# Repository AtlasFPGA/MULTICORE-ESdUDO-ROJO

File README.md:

# MULTICORE-ESdUDO-ROJO
Diseñar la placa - ¡Créalo tu mismo! de coste más reducido para la Fpga CYC1000 con una bluepill STM32F103C8T6

Group ATLAS in Telegram: https://t.me/INICIATIVAATLAS

   Se muestra el multicore en desarrollo para cyc1000 de arrow/trenz el cual aloja una fpga Cyclone 10 LP de intel con 25kles y 66 bloques de Bram de 9Kbytes, tiene integrada una memoria de celular de bajo consumo y reducida latencia, siendo una sdram a 166Mhz con 8MBytes en un bus de 16bits, La familia Cyclone 10 LP permite implementar modelos que superan los 400Mhz en sus diseños, manteniendo un bajo consumo. 
También hay que disponer de una bluepill con un STM32F103C8Tx, posee 64Kbytes de Flash y 20Kbytes de sram, con una unidad de proceso ARM cortex M3 de 32bit funcionando a 72Mhz. 

---
# Esquema analógico totalmente configurable por el usuario en el vídeo compuesto de 512 colores.

Nota:

Creamos una tabla para proceder con el ajuste analógico de la salida de vídeo compuesto.

| R3  |     RV1   | VALOR RESISTIVO RAMA COMPOSITE 0  | R4  | RV2  |  VALOR RESISTIVO RAMA COMPOSITE 1|
|:-------------:|------:|------:|------:|------:|------:|
|750 Ohm|0 Ohm|750 Ohm| 80 Ohm| 0 Ohm|80 Ohm|
|1500 Ohm|1000 Ohm|2500 Ohm|80 Ohm|150 Ohm|230 Ohm|

Para Composite 0 la corriente máxima se obtiene con 750 Ohm -> +3,3V/(750_Ohm)= 0,0044 Amperios

Para Composite 0 la corriente mínima se obtiene con 2500 Ohm -> +3,3V/(2500_Ohm)= 0,00132 Amperios

Para Composite 1 la corriente máxima se obtiene con 80 Ohm -> +3,3V/(80_Ohm)= 0,04125 Amperios -> La CYCLONE 10 LP esta limitada a 12Miliamperios ¿Lo fundimos?

Para Composite 1 la corriente mínima en el diseño propuesto se obtiene con 230 Ohm -> +3,3V/(230_Ohm)= 0,014347926 Amperios -> Por encima de la limitación de corriente 12Miliamperios

Luego hay que calcular que valores de resistencia usar, en Composite 1 en las dos posiciones extremas se drena más corriente por pin.
También vemos que aporta más corriente Composite1 un valor más fuerte que Composite0, por lo que tenemos bien ordenadas las lineas por donde van las señales, pero al ser hardware programable, imaginamos que nos equivocamos, esta es una de las grandes cualidades de una FPGA, con una simple reordenadión de pineado y reetiquetado todo funciona perfectamente,es por esto que muchos diseños actualmente son programables ya sean microcontroladores, cplds o fpgas.

Luego la pregunta es, que resistencia en serie a +3,3V coloco para no fundir un pin de... ¿la preciada FPGA?
doce miliamperios = 0,012_Amperios = +3,3_Voltios/Resistencia_protección_pin

Resistencia_protección_pin = 275 Ohm

Es lo más importante dado que la FPGA tiene limitada la cantidad de corriente que es capaz de entregar, y hacerle una conexión muy baja en resistencia puede fundir o dicho pin o parte de los pines de salida de la fpga, raramente toda la FPGA.

Sus resistencias se suman, la posición de las resistencias fijas es para proteger los circuitos y limitar la corriente, en realidad hemos puesto el valor represantado con el mayor valor resistivo y el menor de todos.

# Pero como siempre pasa os he mentido, porque... ¿Realmente llega a 0V cuando el televisor recoge la señal?

El caso de los condensadores/capacitores de filtrado es algo más complejo dado que las ramas que estan en serie siguen esta ley (Condensador=Capacitor):
1/Condensador_equivalente = 1/Condensador_serie1 + 1/Condensador_serie2 + 1/Condensador_serie3 + ... + 1/Condensador_serieN
Pero como vamos a usar valores del mismo condensador tenemos una rama preparada en serie.
El condensador usado para el montaje son 6 condensadores de 22 pico faradios, ya ser verán si se colocan todos o no, una capacidad bastante pequeña.
1 Mili = 0'001 Faradios
1 Nano = 0'000001 Faradios
1 Pico = 0'000000001 Faradios

Entondes en realidad usamos condensadores/capacitores de:
22 Pico Faradios = 0'000000022 Faradios

cuando hacemos y despejamos esta ecuación 1/Faradios_rama_serie = 1/0'000000022_F + 1/0'000000022_F
Sale un resultado de Faradios_rama_serie = 1/0'000000011 Faradios y en lenguaje de pico -> 11 pico Faradios

Cuando hay condensadore/capacitores en paralelo se suman sus capacidades:
Podemos no filtrar la señal -> 0Faradios pero esto nunca se cumple y menos con señales generadas a tanta frecuencia las pistas siempre tienen un contenido continuo de capacitancia, por eso siempre aparecen modelizaciones de spice.

Usando los 2 condensadores en una sola rama en serie:
Una capacidad de 11 Pico faracios.

Poniendo un Condensador de 22 picofaracios entre la señal de salida de la fpga y GND.
Una capacidad de 22 Pico faradios.

Poniendo los 2 condensadores en paralelo se suman sus capacidades, (Tampoco es verdad si los condensaores estan limitados en voltaje):
Pero bueno digamos que todo es ideal y son 44 Pico Faradios.

La maxima capacidad es usar 2 condensadores en paralelo más una rama de condensadores en serie:
22 Pico Faradios + 22 Pico Faradios + 11 Pico Faradios = 55 Pico Faradios.

Luego con 4 condensadores en la disposición del circuito podemos tener estas capacidades.

Practicamente 0 Faradios , 0'000000022 Faradios,0'000000033 Faradios ,0'000000044 Faradios y 0'000000055 Faradios
Hay un modo que he puesto su filtrado pero no esta explicado.
Pero se vé lo útil de tener la dispoción de filtrado en capacidad, por supuesto si alguien quiere filtrar más la señal puede cambiando los modelos de condensador.

Las resistencias tienen un valor fijo en R3 y R4 y al menos tendrían que limitar la corriente al máximo que permite la familia Cyclone 10 Lp.
---
# Esquema ESdUDO V0101

---
# Capas de la placa ESdUDO V0101

---

   Este modelo implementa soluciones de muy baja latencia, al usar envoltorios con máquinas de estado finito para el video compuesto y el teclado.
   
###   https://github.com/TheSonders/COLOR_PAL
   
###   https://github.com/TheSonders/USBKeyboard

   El diseño es de reducido tamaño, permitiendo alojarlo en equipos estropeados y no recuperables.

   En precio asociado a la placa son aproximadamente 6€.
---

#   Una lista de los pocos componentes necesarios

| Unidades  |     descripción      |  Precio medio en tienda física en España |
|----------|:-------------:|------:|
| 8 |  • condensadores de filtrado, ramas serie y paralelo. | ?€|
| 4 |  • resistencias. Dos de ellas prescindibles mediante programacion de pull down en las patillas K1 y L1 de la cyc1000. |  ?€ |
| 2 | • potenciometros de señal para ajustar la intensidad. |    ?€ |
  | numerosos | • Asi como bastantes tiras de pines, machos y hembras también pines apilables usados en arduino. |    ?€ |
  | 1 | • Un condensador electrolítico. |    ?€ |
  | 1 | • Un pulsador. |    ?€ |
  | 1 | • Un puerto usb A. |    ?€ |
  | 1 | • Un puerto de vídeo compuesto. |    ?€ |
  | 1 | • Disponer de una muestra de cyc1000 del programa Europero de fpgas de intel/arrow. |    ?€ |
  | 1 | • Disponer de una bluepill. |    ?€ |
  | 1 | • Así como un módulo i2s de texas instruments MCP5102A. |    ?€ |

--- 
   Es con diferencia el sistema multicore más económico.

Las placas necesarias:

# ¡ATENCIÓN A LA BLUPILL COLOCADA! 
# HAY DOS MODELOS DE BLUEPILL, LA BLUEPILL PLUS, Y LA PRIMERA BLUEPILL.

BLUEPILL STM32F103C8T6 (Usada en el DISEÑO V0101):

https://es.aliexpress.com/item/1005003429884084.html

BLUEPILL STM32F103C8T6 Plus (Necesita adaptación una linea de 5V existe en lugar de GND, se producirá un buen corto si se opta por este modelo),
por lo demás es compatible en un rango de funcionamiento del 99% y tiene un punto que para el programador es interesante  duplica la flash disponible 128Kbytes.

https://m.es.aliexpress.com/item/1005004918334754.html

SD+TFT AZ-Delivery de 1,8Pulgadas:

https://es.aliexpress.com/item/1005005060814683.html

CYC1000 versión mejorada del 2023 TEI0003-03-QFCR4A-CYC1000:

https://shop.trenz-electronic.de/en/TEI0003-03-QFCR4A-CYC1000-with-Cyclone-10-FPGA-8-MB-SDRAM-8-MB-Flash-6.15-x-2.5-cm?c=480

O una muestra en el programa europeo de microfpgas:

https://www.arrow.com/en/family/intel-solutions-europe

Grupo de la iniciativa ATLAS en TELEGRAM:

# https://t.me/INICIATIVAATLAS

Licencia CERN OHL V2 STRICT:

https://ohwr.orgcern_ohl_s_v2.txt

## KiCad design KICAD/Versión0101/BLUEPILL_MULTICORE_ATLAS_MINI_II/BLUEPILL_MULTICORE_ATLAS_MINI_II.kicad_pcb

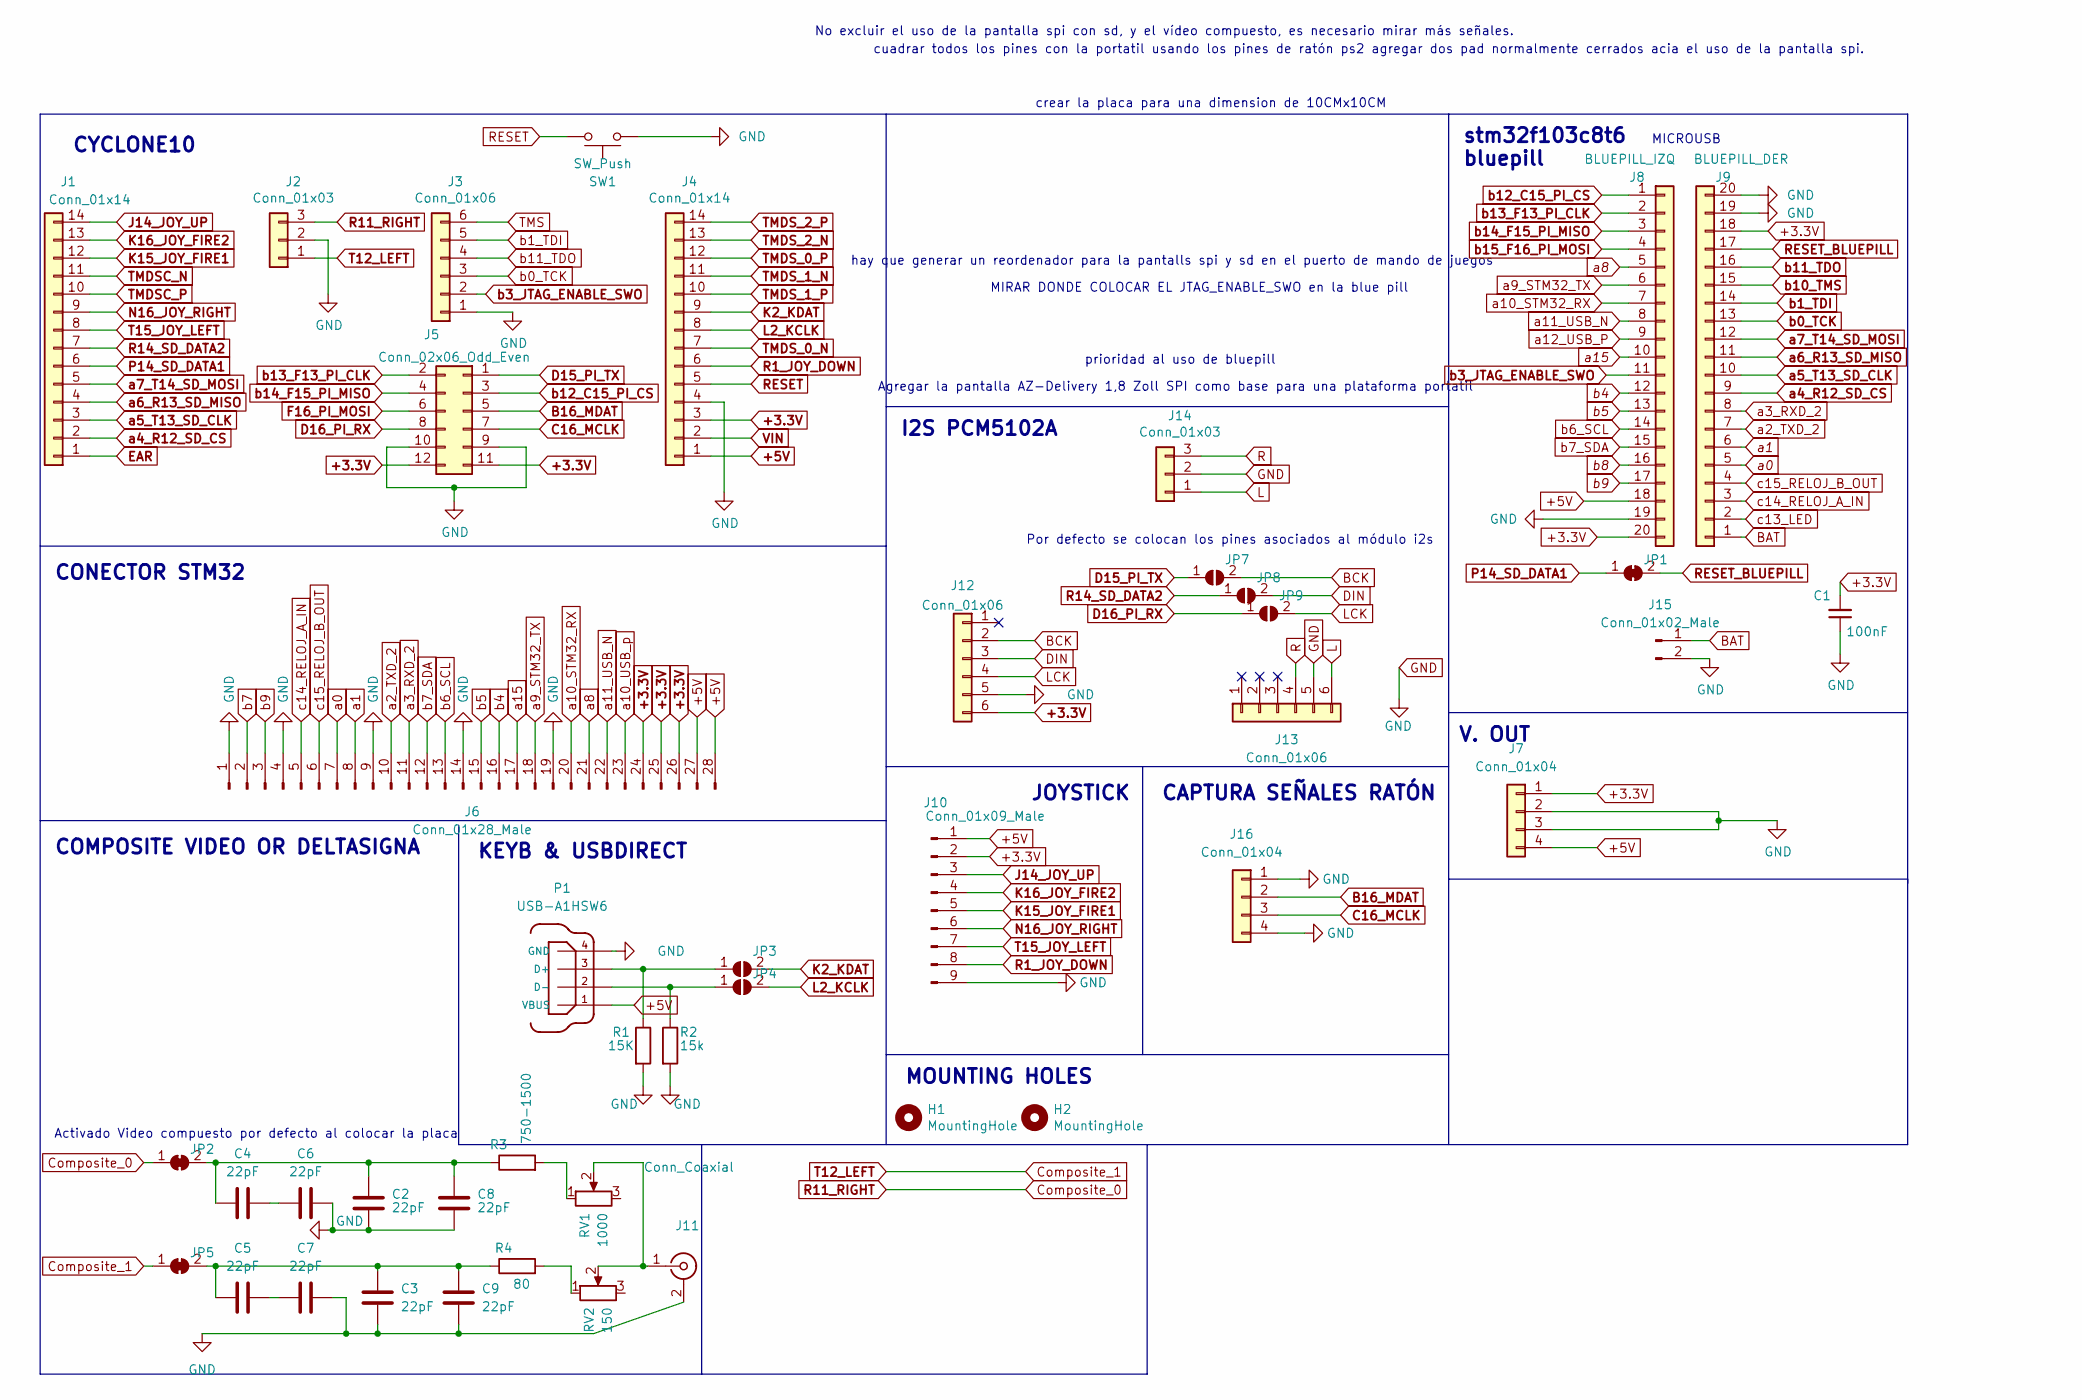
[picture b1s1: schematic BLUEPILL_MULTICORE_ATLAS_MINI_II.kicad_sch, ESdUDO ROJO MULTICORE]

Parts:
C1: 100nF; CP_Radial_D6.3mm_P2.50mm
C2, C3, C4, C5, C6, C7, C8, C9: 22pF; CP_Radial_Tantal_D4.5mm_P2.50mm
H1, H2: MountingHole; MountingHole_3.2mm_M3
J1, J4: Conn_01x14; PinSocket_1x14_P2.54mm_Vertical
J2, J14: Conn_01x03; PinSocket_1x03_P2.54mm_Vertical
J3: Conn_01x06; PinSocket_1x06_P2.54mm_Vertical
J5: Conn_02x06_Odd_Even; PinSocket_2x06_P2.54mm_Vertical
J6: Conn_01x28_Male; PinHeader_1x28_P2.54mm_Horizontal
J7, J16: Conn_01x04; PinHeader_1x04_P2.54mm_Vertical
J8: BLUEPILL_IZQ; PinSocket_1x20_P2.54mm_Vertical
J9: BLUEPILL_DER; PinSocket_1x20_P2.54mm_Vertical
J10: Conn_01x09_Male; PinHeader_1x09_P2.54mm_Vertical
J11: Conn_Coaxial; rca_combined
J12, J13: Conn_01x06; PinHeader_1x06_P2.54mm_Vertical
J15: Conn_01x02_Male; PinSocket_1x02_P2.54mm_Horizontal
JP1, JP2, JP5: SolderJumper_2_Bridged; SolderJumper-2_P1.3mm_Bridged2Bar_RoundedPad1.0x1.5mm
JP3, JP4, JP7, JP8, JP9: SolderJumper_2_Open; SolderJumper-2_P1.3mm_Open_RoundedPad1.0x1.5mm
P1: USB-A1HSW6; OST_USB-A1HSW6
R1: 15K; R_Axial_DIN0309_L9.0mm_D3.2mm_P2.54mm_Vertical
R2: 15k; R_Axial_DIN0309_L9.0mm_D3.2mm_P2.54mm_Vertical
R3: 750-1500; R_Axial_DIN0309_L9.0mm_D3.2mm_P2.54mm_Vertical
R4: 80; R_Axial_DIN0309_L9.0mm_D3.2mm_P2.54mm_Vertical
RV1: 1000; Potentiometer_Bourns_3339H_Vertical
RV2: 150; Potentiometer_Bourns_3339H_Vertical
SW1: SW_Push; SW_PUSH_6mm

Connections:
+3.3V: C1.2, J4.3, J5.11, J5.12, J6.24, J6.25, J6.26, J7.1, J8.20, J9.18, J10.2, J12.6
+5V: J4.1, J6.27, J6.28, J7.4, J8.18, J10.1, P1.1 (VBUS)
B16_MDAT: J5.5, J16.2
BAT: J9.1, J15.1
BCK: J12.2, JP7.2 (B)
C16_MCLK: J5.7, J16.3
Composite_0: J2.3, JP2.1 (A)
Composite_1: J2.1, JP5.1 (A)
D15_PI_TX: J5.1, JP7.1 (A)
D16_PI_RX: J5.8, JP9.1 (A)
DIN: J12.3, JP8.2 (B)
EAR: J1.1
F16_PI_MOSI: J5.6
GND: C1.1, C2.2, C3.2, C6.2, C7.2, C8.2, C9.2, J2.2, J3.1, J4.4, J5.9, J5.10, J6.1, J6.4, J6.9, J6.14, J6.19, J7.2, J7.3, J8.19, J9.19, J9.20, J10.9, J11.2 (Ext), J12.5, J13.5, J14.2, J15.2, J16.1, J16.4, P1.4 (GND), R1.2, R2.2, SW1.2
J14_JOY_UP: J1.14, J10.3
K2_KDAT: J4.9, JP3.2 (B)
K15_JOY_FIRE1: J1.12, J10.5
K16_JOY_FIRE2: J1.13, J10.4
L: J13.6, J14.1
L2_KCLK: J4.8, JP4.2 (B)
LCK: J12.4, JP9.2 (B)
N16_JOY_RIGHT: J1.9, J10.6
unnamed: C2.1, C4.1, C8.1, JP2.2 (B), R3.1
unnamed: C3.1, C5.1, C9.1, JP5.2 (B), R4.1
unnamed: C4.2, C6.1
unnamed: C5.2, C7.1
unnamed: J11.1 (In), RV1.2, RV2.2
unnamed: JP3.1 (A), P1.3 (D+), R1.1
unnamed: JP4.1 (A), P1.2 (D-), R2.1
unnamed: R3.2, RV1.1
unnamed: R4.2, RV2.1
P14_SD_DATA1: J1.6, JP1.1 (A)
R: J13.4, J14.3
R1_JOY_DOWN: J4.6, J10.8
R14_SD_DATA2: J1.7, JP8.1 (A)
RESET: J4.5, SW1.1
RESET_BLUEPILL: J9.17, JP1.2 (B)
T15_JOY_LEFT: J1.8, J10.7
TMDSC_N: J1.11
TMDSC_P: J1.10
TMDS_0_N: J4.7
TMDS_0_P: J4.12
TMDS_1_N: J4.11
TMDS_1_P: J4.10
TMDS_2_N: J4.13
TMDS_2_P: J4.14
TMS: J3.6
VIN: J4.2
a0: J6.7, J9.5
a1: J6.8, J9.6
a2_TXD_2: J6.10, J9.7
a3_RXD_2: J6.11, J9.8
a4_R12_SD_CS: J1.2, J9.9
a5_T13_SD_CLK: J1.3, J9.10
a6_R13_SD_MISO: J1.4, J9.11
a7_T14_SD_MOSI: J1.5, J9.12
a8: J6.21, J8.5
a9_STM32_TX: J6.18, J8.6
a10_STM32_RX: J6.20, J8.7
a10_USB_p: J6.23
a11_USB_N: J6.22, J8.8
a12_USB_P: J8.9
a15: J6.17, J8.10
b0_TCK: J3.3, J9.13
b1_TDI: J3.5, J9.14
b3_JTAG_ENABLE_SWO: J3.2, J8.11
b4: J6.16, J8.12
b5: J6.15, J8.13
b6_SCL: J6.13, J8.14
b7: J6.2
b7_SDA: J6.12, J8.15
b8: J8.16
b9: J6.3, J8.17
b10_TMS: J9.15
b11_TDO: J3.4, J9.16
b12_C15_PI_CS: J5.3, J8.1
b13_F13_PI_CLK: J5.2, J8.2
b14_F15_PI_MISO: J5.4, J8.3
b15_F16_PI_MOSI: J8.4
c13_LED: J9.2
c14_RELOJ_A_IN: J6.5, J9.3
c15_RELOJ_B_OUT: J6.6, J9.4

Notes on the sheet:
No excluir el uso de la pantalla spi con sd, y el vídeo compuesto, es necesario mirar más señales.
Por defecto se colocan los pines asociados al módulo i2s
hay que generar un reordenador para la pantalls spi y sd en el puerto de mando de juegos
prioridad al uso de bluepill
MICROUSB
stm32f103c8t6 bluepill
I2S PCM5102A
CYCLONE10
KEYB & USBDIRECT
Agregar la pantalla AZ-Delivery 1,8 Zoll SPI como base para una plataforma portatil
V. OUT
crear la placa para una dimension de 10CMx10CM
COMPOSITE VIDEO OR DELTASIGNA
Activado Video compuesto por defecto al colocar la placa
CAPTURA SEÑALES RATÓN
MIRAR DONDE COLOCAR EL JTAG_ENABLE_SWO en la blue pill
MOUNTING HOLES
JOYSTICK
cuadrar todos los pines con la portatil usando los pines de ratón ps2 agregar dos pad normalmente cerrados acia el uso de la pantalla spi.
CONECTOR STM32

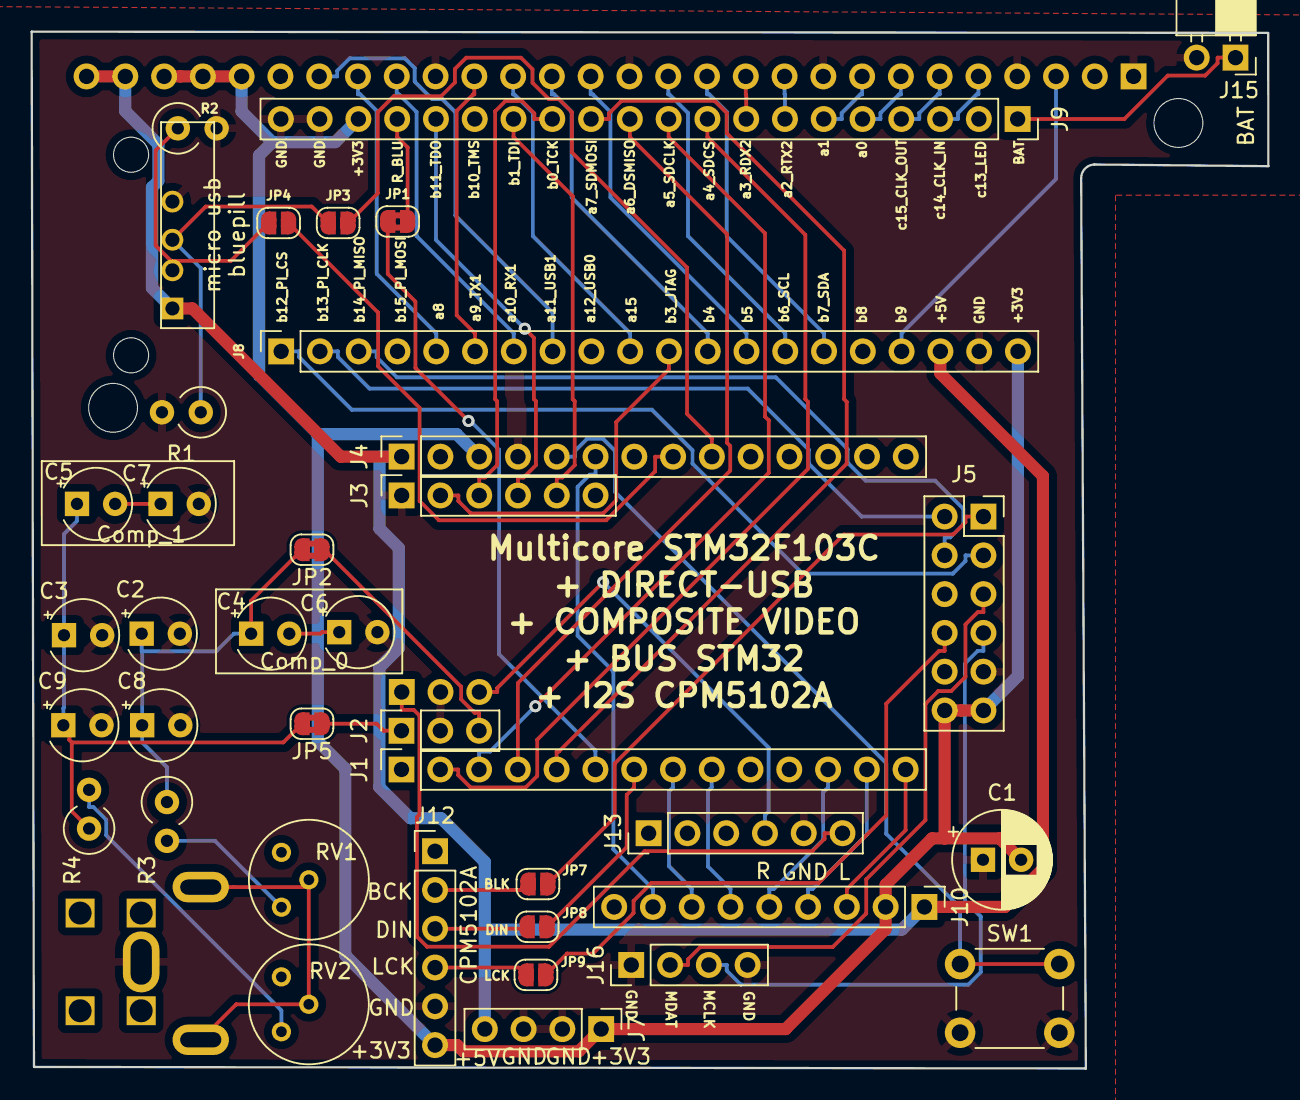
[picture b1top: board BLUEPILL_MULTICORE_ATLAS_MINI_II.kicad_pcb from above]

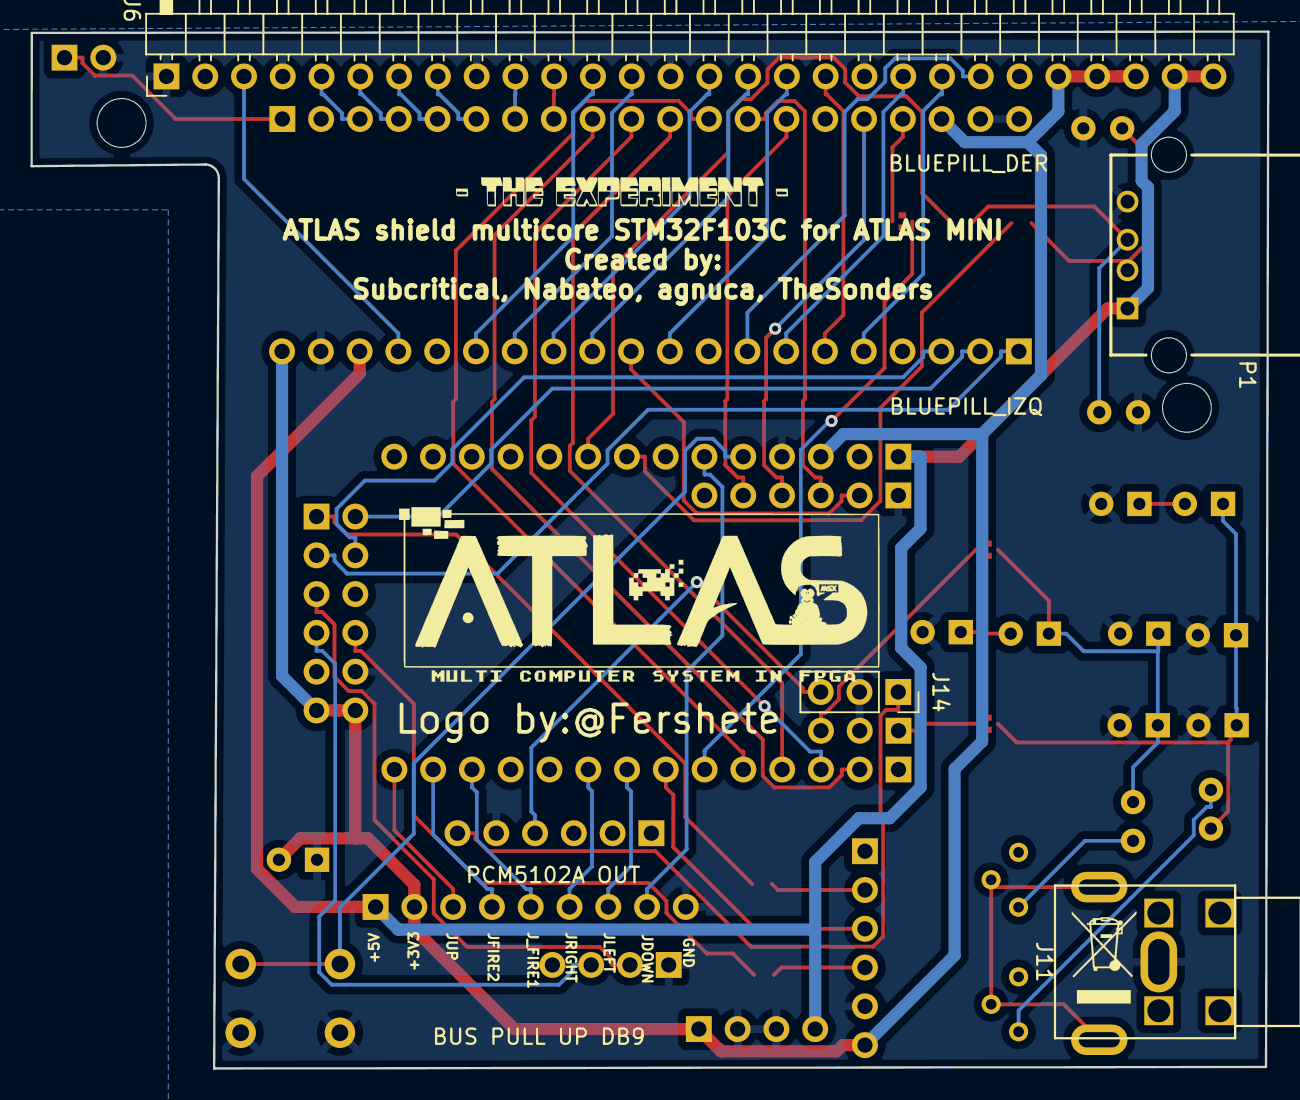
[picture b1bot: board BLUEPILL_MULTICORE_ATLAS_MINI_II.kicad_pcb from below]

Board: 2 copper layers, 81.0 x 67.9 mm, 44 parts (5 on the bottom side), 63 nets.

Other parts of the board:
LOGO: The experiment; Logo_Experiment

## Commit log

2023-06-16 Crear la primera información de ESCUDO ROJO la primera placa multicore por debajo de los 10€
2023-06-16 Agregar información del conversor de Digital a analógico de Texas Instrumentes PCM5102A
2023-06-16 Agregar información de ESDUDO ROJO
2023-06-16 Limpiar la información suministrada en el fichero readme, y agregar el dac PCM5102A
2023-06-16 Subir la guía de usuario de la microfpga CYC1000
2023-06-16 Agregar información sobre el chip asociado a la pantalla recomendada, chips spi para pantallas TFTs ST7789 y ST7735 del fabricante Samsung.
2023-06-16 Mejorar la redacción de ESDUDO-ROJO
2023-06-16 Crear tabla con los pocos componentes necesarios.
2023-06-16 Crear direcctorio de kicad del ESdUDO Multicore
2023-06-16 Posicionamiento de la primera versión remitida a GITHUB.
2023-06-16 Agregar información al diseño de Kicad
2023-06-16 Agregar información al diseño de Kicad en este caso huellas muy usadas entre ellas el Euroconector
2023-06-16 Multitud de modelos 3d, entre ellos la modelización del vídeo compuesto, bus internacional por excelencia para mostrar imágen, el origen de lo retro.
2023-06-16 Posición donde estan las sesiones de spectra.
2023-06-16 las sesiones de spectra de la versión 0101 de ESdUDO ROJO.
2023-06-16 Directorio donde se alojan los modelos 3D de un usb A estandarizado, y su simbolo como huella asociada.
2023-06-16 Modelo USB usado para la representación tridimensional del Multicore ESdUDO ROJO.
2023-06-16 Directorio donde se encuentra la versión 0101, queda limpiarla y reordenar todo el proyecto.
2023-06-16 Ficheros del proyecto ESdUDO Versión 0101, queda mucho por mejorar, pero este es un primer avance.
2023-06-16 Directorio donde alojamos las imágenes del proyecto ESdUDO.
2023-06-16 Diseño de una salida totalmente analógica para el vídeo compuesto
2023-06-16 Agregada información sobre la configuración del vídeo compuesto totalmente configurable de ESdUDO ROJO.
2023-06-16 Posición donde se alojan los diagramas y la pcb con todas las capas en formato pdf.
2023-06-16 Agrego los diagramas y la placa ESdUDO ROJO con todas las capas, ambas en formato pdf.
2023-06-16 Subidos pantallazos de la Versión 0101 de la placa ESdUDO ROJO.
2023-06-16 Agregar información referente a la placa y diagrama del ESdUDO
2023-06-17 Corregir fallos en el encabezado de la descripción
2023-06-17 Modificada entrada de compra económica de BLUEPILL
2023-06-17 Aclarar que se necesita una ligera modificación para el uso de la BLUEPILL PLUS
2023-06-17 Subida versión para blupill clásica y con corrección licencia
    Aclarar que la licencia es la licencia más fuerte CERN OHL S V2:
    Licencia:
    https://ohwr.orgcern_ohl_s_v2.txt
2023-06-17 Corregir información sobre la licencia del proyecto
    CERN OHL V2 STRICT
    https://github.com/AtlasFPGA/MULTICORE-ESDUDO-ROJO/blob/main/Fotos/Esquema_ESdUDO_ROJO_V0101-Correcci%C3%B3n_Licencia.png
2023-06-17 Aclaración licencia CERN OHL V2 STRICT
2023-06-17 Agregar información sobre el mundo de la BLUEPILL
2023-06-17 Modificación rutas
2023-06-17 agregar correcto esquema para la version V0101
2023-06-17 Borrar esquema antiguo
2023-06-17 Mejorar la redacción del README
2023-06-17 Añadir información sobre licencia CERN OHL V2 STRICT README.md
2023-06-17 Ultima versión correcta de cache lib de kicad ESdUDO
2023-06-17 Versión ESdUDO para BLUEPILL original.
2023-06-17 Mejora de la redacción del Léeme de ESdUDO
2023-06-18 En esta carpeta se alojan los ficheros Step tridimensionales usados en la representación del montaje
2023-06-18 Fichero STEP de la CYC1000 TEI0003-02
2023-06-18 Directorio donde esta el step del USB A
2023-06-18 Huella de dos dimensiones y tres dimensiones asociado al USB A
2023-06-18 En este directorio se muestra las huellas bidimensionales y tridimensionales del conector de video compuesto
2023-06-18 Huella 3D del video compuesto tridimensional
2023-06-18 Huella bidimensional RCA
2023-06-18 Agregar información del uso de la matriz de condensadores y resistencia en paralelo con potenciómetro
2023-06-18 Corregir error tabla resistencias salida vídeo compuesto
2023-06-18 Separar frases del cálculo de valores resistivos
2023-06-18 Modificar texto que habla de las corrientes drenadas por pin
2023-06-18 Mejorar explicación de ramas de capacidad en los condensadores
2023-06-18 Mejorar el objetivo de protección de corriente de los pines de la salida de vídeo compuesto.
2023-06-18 La pregunta importante sobre la caída de voltaje en el aparato receptor de la señal.
2023-06-18 Corregir corriente mínima en la linea Composite1
2023-06-18 Fichero Comprimido STEP de la primera BLUEPILL con el STM32F103C8T6
    He comprimido el fichero porque son aproximadamente 80Mbytes de diseño, cuando lo agreguéis al diseño en Kicad, esperar porque tarda un ratín.
2023-06-18 Poner en negrita la dirección de grupo DE INICIATIVA ATLAS
2023-12-11 Group ATLAS in Telegram: https://t.me/INICIATIVAATLAS
2023-12-11 https://t.me/INICIATIVAATLAS -> El grupo ATLAS esta en Telegram pueden encontrarnos allí, Group ATLAS in Telegram

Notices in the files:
KICAD/Versión0101/BLUEPILL_MULTICORE_ATLAS_MINI_II/BLUEPILL_MULTICORE_ATLAS_MINI_II.kicad_pcb:
License CERN OHL V2 STRICT:
